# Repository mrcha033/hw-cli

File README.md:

# hw-codesign: verifiable hardware co-design release pipeline

An agent-facing CLI and MCP server for generating hardware design candidates and
proving which release checks actually ran. It is currently strongest for
**tscircuit/KiCad-backed robotics-controller flows**, not arbitrary board
topologies.

The reusable part today is the gated pipeline: typed specs, deterministic
artifacts, structured failures, provenance, and release policy. The included
component catalog, role set, and end-to-end example are centered on one STM32H7
robotics controller. Supporting a materially different board family currently
requires extending those inputs and, potentially, the generators.

> **Evidence status:** the repository includes generated Gerbers, STEP files,
> BOM, firmware, reports, and a downloadable candidate bundle. It does not yet
> claim a fabricated, electrically brought-up, thermally qualified, or EMC-tested
> board.

---

## Contents

- [Known limits](#known-limits)
- [Run it](#run-it)
- [Current scope](#current-scope)
- [First workflow](#first-workflow)
- [Generated example](#generated-example)
- [Capabilities](#capabilities)
- [Development setup](#development-setup)
- [MCP server](#mcp-server)
- [Distribution](#distribution)
- [Gate semantics](#gate-semantics)
- [Repository layout](#repository-layout)

---

## Known limits

- Three maintained board families are included: the STM32H7 robotics motor
  controller, the ESP32-S3 IoT sensor data logger, and the nRF52840 BLE sensor
  node. All component catalogs are fully reviewed; the ESP32-S3-WROOM-1 symbol
  and footprint were verified against the KiCad `RF_Module` library (2026-06-16).
- The Atopile adapter generates real `.ato` source from the electrical graph and
  runs `ato build`; the compile gate is active. When compile passes,
  `netlist_extract` and `graph_parity` are resolved via source-AST parity (signal
  declarations parsed from the `.ato` file and compared against the electrical
  graph). The three remaining post-compile gates (footprint parity, layout,
  manufacturing export) are `blocked` pending a configured KiCad plugin path.
- The `reference` and `atopile` backends are candidate-only. `tscircuit` and
  `kicad` are fabrication-release-eligible; `python_netlist` is
  netlist-release-eligible (produces `compiled_netlist.json` + firmware rather
  than Gerbers). All release paths require every configured gate to pass.
- The complete cross-domain flow depends on native KiCad, OpenCASCADE,
  Freerouting, tscircuit, and Zephyr tooling. Validated paths: Linux container
  (CI, `ubuntu-latest`), macOS (`make toolchains`), and Windows (Python test
  suite via `windows-latest` CI — native toolchains not yet installed on Windows
  runners).
- Digital gates cannot certify fabrication quality, load thermals, EMI/EMC,
  vibration, abuse safety, ingress protection, transients, or connector life.
  These physical qualification gaps are stated explicitly in every generated
  report and cannot be closed by software.
- The tracked `r1` export is historical digital evidence. The current checked-in
  `reference` configuration is candidate-only and its release gate is expected to
  remain blocked unless a compiled backend is selected and all native gates pass.

---

## Run it

**No Python required — download a standalone binary** from the
[latest release](../../releases/latest):

| Platform | File |
|---|---|
| Linux x86-64 | `hw-{version}-linux-x86_64.tar.gz` |
| macOS arm64 | `hw-{version}-macos-arm64.tar.gz` |
| Windows x86-64 | `hw-{version}-windows-x86_64.zip` |

Each archive contains `hw` (CLI) and `hw-mcp` (MCP server). macOS users must
clear Gatekeeper quarantine after download: `xattr -d com.apple.quarantine ./hw ./hw-mcp`.

These binaries are the lightweight CLI and MCP distribution. Native release gates
(KiCad fabrication, Freerouting, Zephyr) require the container or locally installed
toolchains — the same limitation as the Python package.

**Or run directly with uv** (no install):

```bash
# MCP server
HW_PLATFORM_ROOT="$PWD" uvx --from 'hw-codesign-platform[mcp]' hw-mcp

# CLI
uvx --from hw-codesign-platform hw --root . create-project quadruped_robot_controller
```

**For full toolchains** (KiCad, OpenCASCADE, Freerouting, tscircuit, Zephyr):

```bash
docker run --rm -v "$PWD:/workspace" ghcr.io/mrcha033/hw-cli:latest \
  export-review quadruped_robot_controller
```

New here? Follow [Zero to first candidate report](docs/first-run.md). Before
interpreting a green or blocked result, read the
[validation contract](docs/validation-contract.md). To change the included
design safely, read [Adapting the specification](docs/adapting-a-spec.md).

Missing `kicad-cli` returns `blocked`. Missing OpenCASCADE returns `blocked`.
A compiled error element in tscircuit returns `fail`. An unresolved critical
assumption blocks release. Decoupling proximity not yet modelled is reported as
explicitly deferred, not silently green. **Nothing is assumed to have worked.**

```json
{
  "gate": "tscircuit_compile",
  "status": "blocked",
  "failures": [{"code": "tool_unavailable", "message": "tscircuit compiler not found"}]
}
```

vs.

```json
{
  "gate": "tscircuit_compile",
  "status": "pass",
  "metrics": {"error_elements": 0, "pad_count": 183, "route_count": 217}
}
```

The difference is observable in JSON and enforced by the release gate.

---

## Current scope

A command-line and MCP-server platform that takes a structured YAML spec and
produces a release bundle — Gerbers, STEP, BOM, firmware source, Zephyr
devicetree — only after every configured gate reaches `pass`. Reference
designs produce `candidate` artifacts and are explicitly blocked from release.
Physical qualification risks (load thermals, EMI/EMC, vibration, abuse) are
stated as explicit gaps in every generated report and cannot be closed by
software.

Three reference designs are included:

- **Robotics motor controller** — 4-layer PCB, STM32H7, 12 motor channels, CAN, 24 V VBAT
- **IoT sensor data logger** — 2-layer PCB, ESP32-S3-WROOM-1, USB-C power, I2C IMU (template: `sensor_data_logger`)
- **BLE sensor node** — 2-layer PCB, nRF52840-QIAA, LiPo charging (BQ24079 + BQ27441 + AP2112K), SHT31, 50×35 mm (template: `ble_sensor_node`)

### Backend maturity

| Backend | What works | Release position |
|---|---|---|
| KiCad | Native netlist, ERC/DRC, Freerouting round trip, and manufacturing export | Fabrication-release-eligible when every native gate passes |
| tscircuit | Pinned offline compile, Circuit JSON, graph/footprint parity, placement and routing checks | Fabrication-release-eligible with the KiCad manufacturing bridge and native gates |
| python_netlist | Deterministic netlist and parity checks; produces `compiled_netlist.json` + firmware | Netlist-release-eligible; layout and manufacturing gates are N/A (not blocking) |
| reference | Generates the included design intent and candidate artifacts | Candidate-only; used for tutorials and pipeline inspection |
| Atopile | Generates real `.ato` source; compile, netlist_extract, and graph_parity gates active; source-AST parity checks declared signals vs graph | Candidate-only; footprint/layout/manufacturing blocked pending KiCad plugin path |

This is not yet universal hardware design automation. Within the included
robotics-controller family, users can change supported electrical, mechanical,
firmware, sourcing, and manufacturing parameters. A new topology requires a new
role set/component catalog and may require generator changes; see the adaptation
guide.

---

## First workflow

The shortest useful workflow intentionally ends in a `blocked` result while
still producing a reviewable candidate:

```bash
uvx --from hw-codesign-platform hw --root . create-project first_board
uvx --from hw-codesign-platform hw --root . iterate first_board --no-external
uvx --from hw-codesign-platform hw --root . export-review first_board
```

Expected result:

```json
{
  "status": "blocked",
  "iteration_id": "0001",
  "candidate": {
    "status": "candidate",
    "candidate_only": true
  }
}
```

`blocked` means the system preserved the candidate but refused to call it a
release. The command writes specs, generated intent and source, gate reports,
an iteration snapshot, and a candidate ZIP under `projects/first_board/`. The
full file map and interpretation are in the first-run guide.

---

## Generated example

The tracked robotics-controller example provides inspectable output without
requiring a local toolchain run:

- [Example and proof index](examples/robotics-motor-controller/README.md)
- [Complete generated bundle](projects/quadruped_robot_controller/exports/quadruped_robot_controller-r1.zip)
- [Gerbers](projects/quadruped_robot_controller/exports/r1/fabrication/gerbers.zip)
- [BOM](projects/quadruped_robot_controller/exports/r1/fabrication/bom.csv)
- [Assembly STEP](projects/quadruped_robot_controller/exports/r1/mechanical/assembly.step)
- [Validation report](projects/quadruped_robot_controller/exports/r1/docs/validation_report.json)
- [Known physical risks](projects/quadruped_robot_controller/exports/r1/docs/known_risks.md)

These are generated design artifacts and digital evidence, not proof of
fabrication or physical qualification. The current checked-in project spec uses
the candidate-only `reference` backend, so rerunning its current release gate is
expected to block until a compiled backend and all native gates are selected and
passed.

### Adoption milestones still open

- Publish a report screenshot or demo recording from a stable release workflow.
- Fabricate and bring up a generated board, then publish photographs, measured
  results, deviations, and the exact artifact bundle sent to manufacturing.
- Record thermal, transient, EMI/EMC, vibration, and connector qualification as
  physical evidence rather than software gate output.

---

## Capabilities

### Electronics topology authoring
- Agents author circuit blocks via `hw_add_circuit_block`: specify a ref,
  category, and connection map; the block is merged into the base topology, nets
  are re-derived, and ERC runs immediately — the gate result is returned in the
  same response
- `hw_propose_circuit_block` searches the curated component catalog by category
  and returns candidates with BOM-resolution status before any block is committed
- Agent-authored blocks stored under `agent_electronics.blocks` in
  `spec/agent_blocks.yaml`; distinct key prevents collision with `system.yaml`
  during spec merge
- ERC tolerates single-pin nets when every endpoint belongs to an agent block
  (incremental authoring support)

### Electronics backends
- Deterministic typed electrical graph with role-set resolver and curated
  component database; every resolved component has immutable provenance
- Shared source-generation step plus six-gate backend contract (compile →
  netlist → graph parity → footprint parity → layout → manufacturing export)
  enforced across all adapters
- Offline pinned **tscircuit 0.1.1491** PCB compile: Circuit JSON netlist, pad,
  placement, routing, and error-element validation
- **KiCad-native** adapter: native XML netlist extraction, ERC/DRC, Freerouting
  2.2.4 autoroute (DSN/SES round-trip), and Gerber/drill/position/BOM/STEP export
- **Python-netlist** adapter: netlist-release-eligible; produces
  `compiled_netlist.json` + firmware; layout and manufacturing gates are N/A
  rather than blocking — the release tier is explicitly `"netlist"` not fabrication
- **Atopile** adapter: emits `.ato` source and runs `ato build`; when compile
  passes, `netlist_extract` and `graph_parity` are resolved via source-AST parity;
  footprint/layout/manufacturing remain blocked pending a KiCad plugin path
- KiCad CLI and Zephyr `west` adapters with structured `tool_unavailable` reports
  when the tool is absent — they do not silently skip

### Placement
- Agent-authored placement constraints via `hw_set_placement_constraint`:
  express relationships (`adjacent_to`, `near_connector`) rather than absolute
  XY coordinates; the placer derives positions and the `placement_constraints`
  gate validates compliance immediately on write
- Constraint-driven placement proposal: structured, provenance-tagged placements
  with keepout, mounting-hole, connector-edge, decoupling-proximity, and
  thermal-spacing constraints
- Hard-blocks on off-board components, coincident centers, and connectors placed
  on the wrong board half; advisory warnings on coarse courtyard overlap and
  thermal spacing
- Decoupling proximity is represented as explicitly unenforced — cap-to-IC
  association is not in the netlist; the gate says so rather than claiming it
  checked something it did not
- Not authoritative: native ERC/DRC and the mechanical interference gate remain
  the release-blocking arbiters

### Mechanical
- Parametric 3D part design via `hw_design_part`: five part types
  (`pcb_mount_bracket`, `standoff_tower`, `cable_clip`, `din_rail_adapter`,
  `custom_enclosure_variant`), each with typed intent fields; parts are exported
  as STEP + STL with an FDM printability report (overhang, min wall, min hole)
- Spec-parameterized OpenCASCADE enclosure variants, mounting plates, frame
  brackets, connector cutouts, and board STEP assembly import/export
- Gates: valid solid, manifold STL, tolerance-aware board/component clearance,
  connector alignment, mounting-hole alignment, and measured BRep interference
  volume — nonzero interference returns `fail`
- Mechanical release requires the board STEP exported by the electronics backend;
  missing evidence returns `blocked`, not a fabricated pass

### Firmware module authoring
- Agents author firmware behavior modules via `hw_design_firmware_module`:
  four parametric behaviors (`timeout_shutdown`, `periodic_transmit`,
  `state_machine`, `sensor_poll`); each emits a `.c` file under
  `firmware/modules/` with matching Zephyr config entries
- `firmware_module_check` gate validates that every referenced signal exists in
  the pinmap; unknown signals return `fail` with specific signal names
- Signal-level cross-domain consistency checked by
  `hw_check_cross_domain_consistency`: placement constraint refs verified against
  BOM, firmware module signals verified against pinmap

### Suppliers and BOM
- Normalized curated, LCSC/JLCPCB, Digi-Key, Mouser, and Octopart-style
  supplier adapters with datasheet evidence and availability gates
- Release checks consume only in-repository snapshots under `parts/suppliers`;
  no implicit network lookup at release time
- Known out-of-stock or discontinued parts fail; missing or stale evidence blocks
- Manufacturer datasheet review evidence hashed into resolved component provenance

### Release
- Release gate requires every configured gate at `pass`, all critical assumptions
  resolved by a human, and every declared artifact present on disk with a matching
  hash
- Fabrication release: `tscircuit` and `kicad` backends (Gerber + drill + STEP);
  netlist release: `python_netlist` backend (`compiled_netlist.json` + firmware);
  `reference` and `atopile` are candidate-only

---

## Development setup

```bash
python3 -m venv .venv
.venv/bin/pip install '.[dev,mcp]'
npm ci --ignore-scripts
.venv/bin/hw --root . create-project quadruped_robot_controller
.venv/bin/hw --root . iterate quadruped_robot_controller --no-external
```

Without native toolchains all external gates return `blocked`. That is the
expected and correct output when the tools are not installed.

Install the pinned native macOS backends and run the complete flow:

```bash
make toolchains
.venv/bin/hw --root . design-until-release quadruped_robot_controller --external
```

---

## MCP server

```bash
HW_PLATFORM_ROOT="$PWD" uvx --from 'hw-codesign-platform[mcp]' hw-mcp
```

Claude Desktop configuration:

```json
{
  "mcpServers": {
    "hw-codesign": {
      "command": "uvx",
      "args": ["--from", "hw-codesign-platform[mcp]", "hw-mcp"],
      "env": {
        "HW_PLATFORM_ROOT": "/absolute/path/to/hardware-workspace"
      }
    }
  }
}
```

The configured workspace must be writable because projects, validation reports,
review bundles, and release artifacts are created beneath it.

### Canonical agent workflow

```
hw_get_capabilities          ← which backends and external tools are installed
hw_create_project / hw_open_project
hw_update_requirements       ← lowers natural-language requirements; returns release_blocking_failures

# Author topology, parts, placement, and firmware (new in Phases A–D)
hw_get_part_types            ← available parametric part types and their intent schemas
hw_design_part               ← design a 3D-printable part; returns STEP/STL + printability report
hw_propose_circuit_block     ← find catalog candidates for a given category before committing
hw_add_circuit_block         ← author a circuit block into the topology; ERC runs immediately
hw_set_placement_constraint  ← express adjacent_to / near_connector relationships; gate runs on write
hw_design_firmware_module    ← author a firmware behavior (timeout_shutdown, periodic_transmit, …)
hw_record_design_decision    ← log a decision + rationale to history/decisions.jsonl
hw_check_cross_domain_consistency ← validate placement refs against BOM, firmware signals against pinmap

hw_generate_all              ← always candidate_only=true, release_eligible=false
hw_run_all_checks            ← include_external=true for full gate matrix
hw_review_release_readiness  ← non-authoritative summary: blocking gates, requirements, assumptions
hw_generate_repair_plan / hw_apply_repair_plan / hw_resolve_assumption
hw_check_release_gate        ← release_eligible=true when status==pass
hw_export_candidate_bundle   ← archive checkpoint (candidate_only=true, release_eligible=false)
hw_export_release_bundle     ← release_eligible=true when status==released; only reachable after gate passes
```

### Response envelope

Every tool response carries a consistent envelope that enforces the core invariant:
**candidate generated ≠ release passed ≠ fabrication qualified.**

| Field | Meaning |
|---|---|
| `release_eligible` | `false` on every tool; `true` only from `hw_check_release_gate` (status `pass`) and `hw_export_release_bundle` (status `released`) |
| `candidate_only` | `true` when the backend or gate state precludes release |
| `release_blocking_failures` | always-present list of strings; empty only when no blockers are known |

`hw_review_release_readiness` additionally carries:

| Field | Meaning |
|---|---|
| `release_gate_authoritative` | always `false` — this tool reads persisted reports; only `hw_check_release_gate` is authoritative |
| `readiness_estimate` | `pass` / `fail` / `blocked` based on persisted reports; not a gate outcome |
| `data_freshness` | `current` / `possibly_stale` / `unknown` — heuristic based on spec vs report file timestamps; `possibly_stale` means the spec was modified after the last check run |

### Tools

**Platform introspection**
- `hw_get_capabilities` — available backends, external tools, and which gates each enables; call before generating
- `hw_diagnose_environment` — detailed environment probe: Python version, toolchain paths, installed packages

**Project / spec**
- `hw_create_project` — create a new project from a template
- `hw_open_project` — open an existing project and return its spec
- `hw_snapshot_project` — snapshot the current project state as a named iteration
- `hw_compare_iterations` — diff two iteration snapshots
- `hw_read_spec` — read the merged project spec
- `hw_validate_spec` — validate the spec against its JSON Schema; returns failures with field paths
- `hw_update_spec` — write a spec section; requires `user_approved=true` for safety-critical sections
- `hw_update_requirements` — lower natural-language requirements into typed spec fields; returns `release_blocking_failures` for unsupported constraints
- `hw_list_assumptions` — list all declared design assumptions and their resolution state
- `hw_resolve_assumption` — resolve a named assumption; requires `approved=true`

**Mechanical part design**
- `hw_get_part_types` — available parametric part types with their intent schemas
- `hw_design_part` — design a 3D-printable part from typed intent; returns STEP/STL + FDM printability report
- `hw_list_parts` — list all agent-designed parts for a project

**Electronics topology authoring**
- `hw_propose_circuit_block` — search component catalog by category; returns candidates before any commit
- `hw_add_circuit_block` — add or replace a circuit block in the topology; ERC gate result returned inline
- `hw_list_circuit_blocks` — list all agent-authored circuit blocks for a project

**Placement constraint authoring**
- `hw_set_placement_constraint` — author a placement relationship (`adjacent_to`, `near_connector`); placement gate runs on write
- `hw_list_placement_constraints` — list all placement constraints for a project

**Firmware module authoring**
- `hw_design_firmware_module` — author a firmware behavior module (`timeout_shutdown`, `periodic_transmit`, `state_machine`, `sensor_poll`); emits `.c` + config; signal refs checked against pinmap
- `hw_list_firmware_modules` — list all agent-designed firmware modules for a project

**Design traceability (Phase E)**
- `hw_record_design_decision` — log a decision + rationale to `history/decisions.jsonl`
- `hw_check_cross_domain_consistency` — validate placement constraint refs against BOM and firmware signal refs against pinmap; returns a GateReport

**Generation** (all emit `release_eligible: false`, `candidate_only: true`)
- `hw_generate_all` — generate electronics, mechanical, and firmware sources in one step
- `hw_generate_reference_intent` — generate reference-backend intent artifacts only
- `hw_generate_electronics_source` — generate electronics source for the configured backend
- `hw_generate_mechanical` — generate mechanical source (enclosure, mounting, fixtures)
- `hw_generate_firmware` — generate Zephyr firmware source (pinmap, devicetree, app scaffold) including any authored modules
- `hw_generate_bringup_tests` — generate bring-up test scripts from the firmware source

**Validation**
- `hw_run_all_checks` — run all configured gates; `include_external=false` skips native toolchain gates
- `hw_check_release_gate` — run the full release gate; `release_eligible=true` only when status is `pass`
- `hw_get_failure_report` — read persisted gate reports from disk; optionally filter by gate name
- `hw_run_erc` — run KiCad-native ERC; returns structured failures
- `hw_run_drc` — run KiCad-native DRC against a named fab profile
- `hw_check_electrical_semantics` — validate electrical graph semantics against spec constraints
- `hw_extract_electrical_graph` — return the resolved electrical graph JSON
- `hw_check_pinmap` — validate firmware pin assignments against the electrical graph
- `hw_check_mechanical_fit` — run mechanical clearance, interference, and alignment checks
- `hw_build_firmware` — invoke `west build` for the Zephyr target; returns structured build result

**Iteration / repair**
- `hw_run_design_iteration` — single supervised generate→check→repair cycle
- `hw_generate_repair_plan` — propose spec patches for current gate failures; includes `agent_actions` list of specific tool calls to address each failure code
- `hw_apply_repair_plan` — apply safe patches automatically; proposals requiring approval are returned, not applied
- `hw_design_until_release` — autonomous generate→check→repair loop; requires `user_approved_autonomous_iteration=true` or returns `blocked`

**Candidate management**
- `hw_export_candidate_bundle` — snapshot and ZIP the current state (`candidate_only=true`, `release_eligible=false`)
- `hw_list_candidates` — list all candidate bundles for a project
- `hw_get_candidate` — retrieve metadata for a specific candidate bundle
- `hw_review_candidate` — structured review of a candidate: gate summary, blocking failures, provenance
- `hw_compare_candidates` — diff two candidate bundles by gate status and artifact hashes

**Release readiness and export**
- `hw_review_release_readiness` — non-authoritative summary from persisted reports; check `readiness_estimate` and `data_freshness` fields
- `hw_check_release_gate` — authoritative gate; the only tool that sets `release_eligible=true`
- `hw_prepare_fabrication_review` — assemble a fabrication review package for external DFM review
- `hw_export_pcb_fabrication` — export PCB fabrication files (Gerber, drill, BOM, pick-and-place); requires KiCad native
- `hw_export_mechanical` — export STEP/STL mechanical files; requires OpenCASCADE
- `hw_import_board_step` — import an externally sourced board STEP into the mechanical assembly
- `hw_export_release_bundle` — ZIP the release directory; sets `release_eligible=true` when status is `released`
- `hw_generate_design_report` — generate a human-readable design report markdown
- `hw_verify_release` — verify artifact integrity of the release directory against its manifest

### MCP resources

URI-template resources for structured reads without tool calls:

| Resource | Contents |
|---|---|
| `hw://project/{project}/release-gate` | Non-authoritative release readiness summary (`release_gate_authoritative: false`; use `hw_check_release_gate` for the authoritative gate) |
| `hw://project/{project}/spec` | Full merged project spec |
| `hw://project/{project}/requirements` | Active requirements: lowered and unresolved constraints |

---

## Distribution

- PyPI publishes `hw-codesign-platform` from semantic-version tags using Trusted
  Publishing.
- GHCR publishes `ghcr.io/mrcha033/hw-cli` with the full native toolchain for
  `linux/amd64`.
- Each GitHub release attaches a canonical `bundle.json` and its
  `review_bundle.schema.json` contract.
- Homebrew is deferred because native system dependencies make the container a
  more reliable installation path.
- conda-forge should be reconsidered when mixed Python/system dependency support
  becomes important to broader electronics-engineering adoption.
- MCP registry publication is deferred until the public tool interface and
  versioning policy are stable.

---

## Gate semantics

| Status | Meaning |
|---|---|
| `pass` | check ran and found no blocking finding |
| `fail` | check ran and found a violation |
| `blocked` | required tooling or prior decision was absent |
| `candidate` | artifact was generated but is not release-eligible |
| `generated` | source or spec was written; does not imply gate passage or release eligibility |
| `released` | all gates passed and the release bundle was exported |

`generated` ≠ `pass` ≠ `released`. Every tool emits `release_eligible: false`
unless it is `hw_check_release_gate` (status `pass`) or `hw_export_release_bundle`
(status `released`).

The complete release, adapter, hash, and physical-evidence rules are defined in
[Validation contract](docs/validation-contract.md).

---

## Repository layout

```
src/hw_codesign/          # core platform and service layer
  backends/               # per-backend adapters (tscircuit, kicad, ...)
    firmware_modules/     # parametric firmware behavior renderers (Phase D)
    parts/                # parametric 3D part designers (Phase A)
schemas/                  # JSON Schema for spec validation
parts/                    # curated component database and supplier snapshots
projects/<name>/          # generated project workspaces
  spec/
    system.yaml           # board topology, backend, supply rails
    agent_blocks.yaml     # agent-authored circuit blocks + placement constraints
  electronics/
  mechanical/
    parts/<part_name>/    # designed 3D parts: intent.json, .step, .stl
  firmware/
    modules/              # agent-authored firmware module .c files
  history/
    decisions.jsonl       # structured design decision log (Phase E)
    iterations/
  validation/reports/
  exports/
```

Digital release evidence cannot certify load thermals, EMI/EMC, abuse safety,
vibration life, motor transients, ingress protection, or connector fatigue.
These remain explicit physical validation gaps in every generated report.

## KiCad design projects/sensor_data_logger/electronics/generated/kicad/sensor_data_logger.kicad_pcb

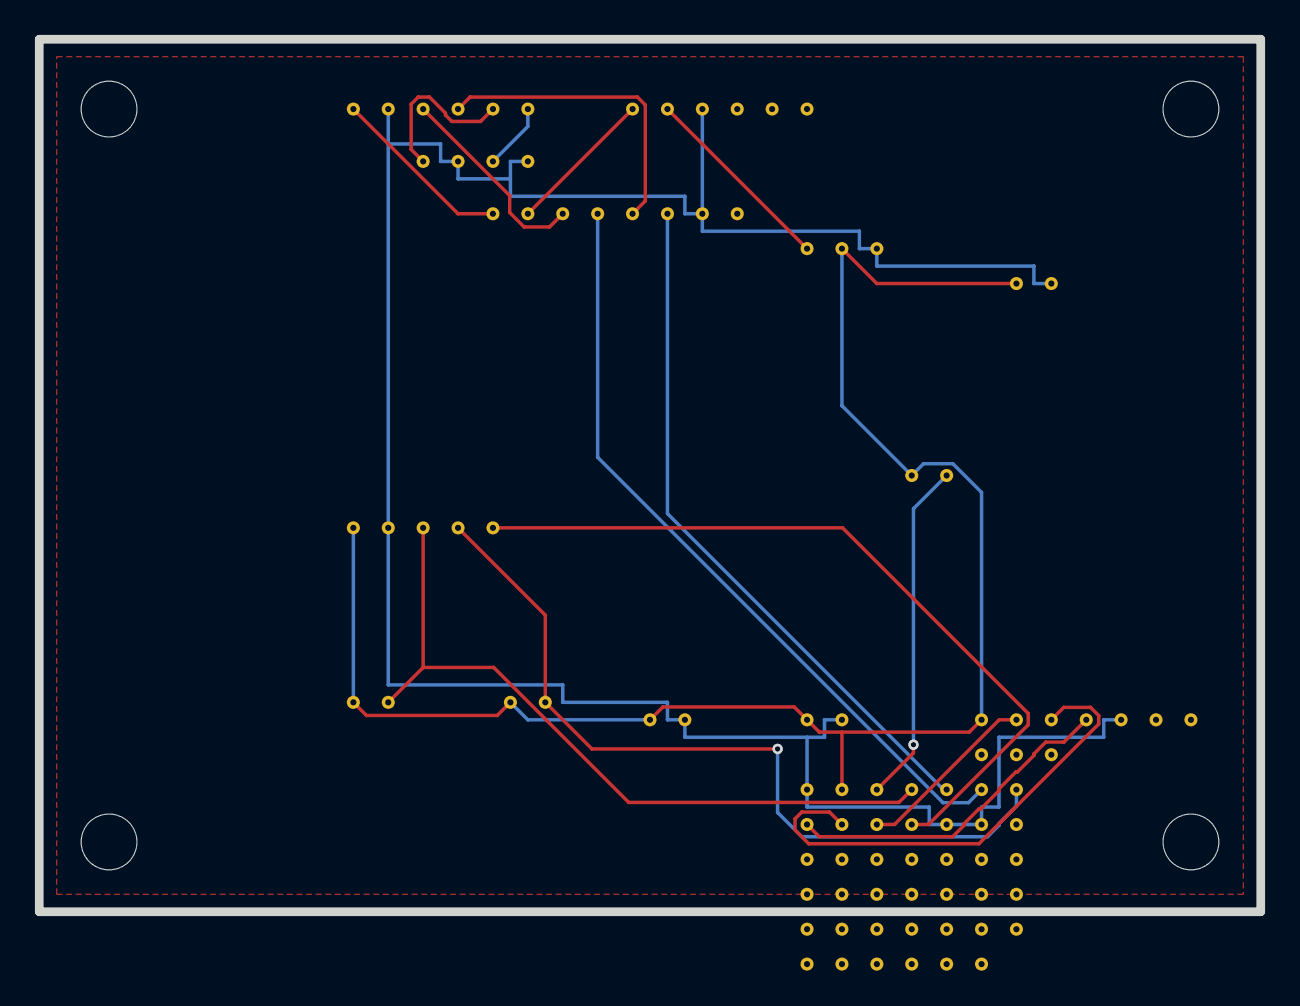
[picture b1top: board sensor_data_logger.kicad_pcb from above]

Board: 2 copper layers, 70.0 x 50.0 mm, 20 parts (0 on the bottom side), 18 nets.

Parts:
C1, C2: 100nF; C_0603_1608Metric
C9: 22uF; C_1206_3216Metric
D1: USB ESD; SOT-23-6
F1: 500mA Fuse; MIDI_Fuse
H1, H2, H3, H4: MountingHole; MountingHole_3.2mm_Pad
J1: USB-C POWER; USB_C_GCT_USB4105
J2: UART DEBUG; FTSH-105
Q1: Ideal Diode; SOT-23-6
R1, R2, R3: 4K7; R_0603_1608Metric
R5, R6: 5K1 USB-C Rd; R_0603_1608Metric
U1: ESP32-S3-WROOM-1
U2: ICM-42688-P; LGA-14
U3: 3V3 Buck; VQFN-16

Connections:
BOOT: J2.4, U1.27
ESP_EN: R3.2, U1.3
GND: C1.2, C2.2, C9.2, D1.5, J1.2, J2.5, Q1.3, R5.2, R6.2, U1.1, U1.40, U1.41, U2.2, U3.3
I2C_IMU_SCL: R1.2, U1.12, U2.3
I2C_IMU_SDA: R2.2, U1.15, U2.4
IMU_INT: U1.39, U2.5
UART_RX: J2.3, U1.36
UART_TX: J2.2, U1.37
USB_CC1: J1.5, R5.1
USB_CC2: J1.6, R6.1
USB_DM: D1.4, U1.13
USB_DM_RAW: D1.3, J1.4
USB_DP: D1.2, U1.14
USB_DP_RAW: D1.1, J1.3
USB_FUSED: F1.2, Q1.1
USB_PROT: Q1.2, U3.1
USB_VBUS: F1.1, J1.1
V3V3: C1.1, C2.1, C9.1, J2.1, R1.1, R2.1, R3.1, U1.2, U2.1, U3.2

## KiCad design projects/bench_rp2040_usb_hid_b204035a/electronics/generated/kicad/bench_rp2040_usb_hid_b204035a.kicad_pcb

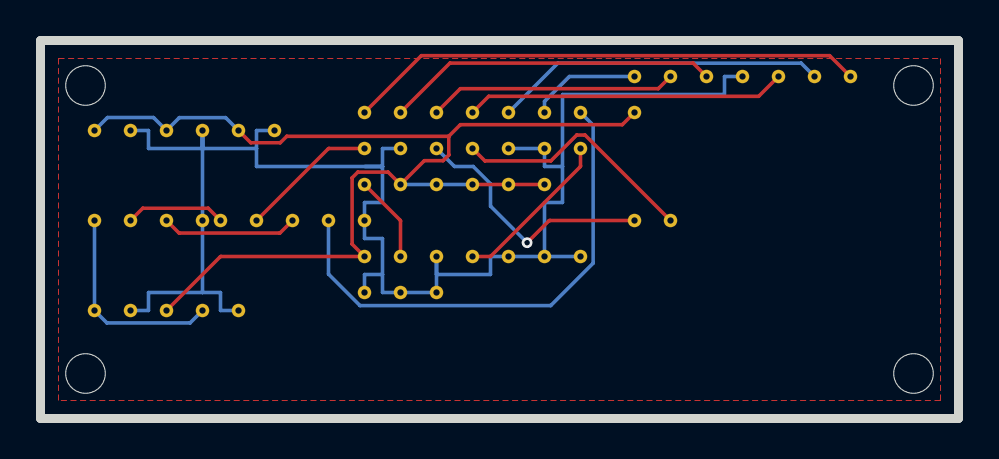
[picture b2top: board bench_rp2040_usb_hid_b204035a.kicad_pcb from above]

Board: 2 copper layers, 51.0 x 21.0 mm, 15 parts (0 on the bottom side), 17 nets.

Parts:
C1, C2: 100nF; C_0402_1005Metric
C3: 10uF; C_0603_1608Metric
C4: 10uF USB_IN; C_0603_1608Metric
D1: USB ESD; SOT-23-6
H1, H2, H3, H4: MountingHole; MountingHole_2.2mm_Pad
J1: USB-C POWER; USB_C_GCT_USB4105
J2: SWD 10-pin; PinHeader_2x05_P2.54mm_Vertical
U1: 3V3 LDO; SOT-23-5
U2: RP2040; QFN-56-1EP_7x7mm_P0.4mm_EP3.2x3.2mm
U3: 2MB QSPI; SOIC-8_3.9x4.9mm_P1.27mm
X1: 12MHz XTAL; Crystal_SMD_HC-49S

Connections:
GND: C1.2, C2.2, C3.2, C4.2, D1.5, J1.4, J2.3, J2.5, J2.6, J2.7, J2.8, J2.9, J2.10, U1.2, U2.16, U2.33, U2.34, U3.4
QSPI_CLK: U2.5, U3.6
QSPI_CS: U2.6, U3.1
QSPI_D2: U2.2, U3.3
QSPI_D3: U2.1, U3.7
QSPI_MISO: U2.3, U3.2
QSPI_MOSI: U2.4, U3.5
SWCLK: J2.4, U2.40
SWDIO: J2.2, U2.41
USB_DM: D1.4, U2.11
USB_DM_RAW: D1.3, J1.3
USB_DP: D1.2, U2.12
USB_DP_RAW: D1.1, J1.2
USB_VBUS: C4.1, J1.1, U1.1
V3V3: C1.1, C2.1, C3.1, J2.1, U1.3, U2.44, U2.45, U2.46, U2.47, U2.48, U3.8
XIN: U2.17, X1.1
XOUT: U2.18, X1.2

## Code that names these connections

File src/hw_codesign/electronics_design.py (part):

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    dp_net = "USB_DP_RAW" if raw_data else "USB_DP"
    dm_net = "USB_DM_RAW" if raw_data else "USB_DM"
    return [
        pin(1, "VBUS", "USB_VBUS", "power_in"),
        pin(2, "GND", "GND", "ground"),
        pin(3, "D+", dp_net, "bidirectional"),
        pin(4, "D-", dm_net, "bidirectional"),
        pin(5, "CC1", "USB_CC1", "passive"),
        pin(6, "CC2", "USB_CC2", "passive"),
    ]


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            "5K1 USB-C Rd",
            "RC0603FR-075K1L",
            "R0603",
            [pin(1, "A", "USB_CC1", "passive"), pin(2, "B", "GND", "ground")],
            manufacturer="Yageo",
            substitute_mpn="CRCW06035K10FKEA",
        ),
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            "5K1 USB-C Rd",
            "RC0603FR-075K1L",
            "R0603",
            [pin(1, "A", "USB_CC2", "passive"), pin(2, "B", "GND", "ground")],
            manufacturer="Yageo",
            substitute_mpn="CRCW06035K10FKEA",
        ),
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    signal_nets = ["ESTOP_IN", "CAN_RX", "CAN_TX", "I2C_IMU_SCL", "I2C_IMU_SDA", "IMU_INT", "SWDIO", "SWCLK", "NRST", "USB_DP", "USB_DM"]
    for index in range(1, channels + 1):
        signal_nets.extend((f"MOTOR{index}_PWM", f"MOTOR{index}_CURRENT", f"MOTOR{index}_ENC"))
    mcu_pins = [pin(1, "VDD", "V3V3", "power_in"), pin(2, "VSS", "GND", "ground")]
    for number, net in enumerate(signal_nets, 3):
        role = "analog" if net.endswith("CURRENT") else "bidirectional"
        mcu_pins.append(pin(number, net, net, role))
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        component("D1", "tvs", "33V TVS", "SMCJ33A", "SMCJ", [pin(1, "K", "VBAT", "passive"), pin(2, "A", "GND", "ground")], manufacturer="Littelfuse", substitute_mpn="SMCJ33A-E3/57T"),
        component("U3", "efuse", "eFuse", "TPS26630RGET", "VQFN24", [pin(1, "IN", "VBAT", "power_in"), pin(2, "OUT", "VSYS", "power_out"), pin(3, "GND", "GND", "ground"), pin(4, "SHDN", "ESTOP_GATE", "input")], manufacturer="Texas Instruments", substitute_mpn="LTC4368IDD-2"),
        component("U4", "regulator", "5V Buck", "LM76005RNPR", "WQFN30", [pin(1, "VIN", "VSYS", "power_in"), pin(2, "VOUT", "V5", "power_out"), pin(3, "GND", "GND", "ground")], manufacturer="Texas Instruments", substitute_mpn="LT8645SIV"),
        component("U5", "regulator", "3V3 Buck", "TPS62133RGTR", "VQFN16", [pin(1, "VIN", "V5", "power_in"), pin(2, "VOUT", "V3V3", "power_out"), pin(3, "GND", "GND", "ground")], manufacturer="Texas Instruments", substitute_mpn="AP63203WU-7"),
        component("U1", "mcu", "STM32H743", "STM32H743VIT6", "LQFP100", mcu_pins, manufacturer="STMicroelectronics", substitute_mpn="STM32H753VIT6"),
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        component("J2", "estop", "E-STOP", "Phoenix-1935161", "Terminal_3Pin", [pin(1, "V3V3", "V3V3", "power_out"), pin(2, "ESTOP", "ESTOP_IN", "input"), pin(3, "GND", "GND", "ground")], manufacturer="Phoenix Contact", substitute_mpn="WAGO-250-203"),
        component("Q2", "safety_gate", "E-STOP GATE", "SN74LVC1G97DBVR", "SOT23-6", [pin(1, "VCC", "V3V3", "power_in"), pin(2, "IN", "ESTOP_IN", "input"), pin(3, "OUT", "ESTOP_GATE", "output"), pin(4, "GND", "GND", "ground")], manufacturer="Texas Instruments", substitute_mpn="74LVC1G97GV"),
        component("J3", "can_connector", "CAN", "Molex-43650-0300", "MicroFit_3Pin", [pin(1, "CANH", "CANH", "bidirectional"), pin(2, "CANL", "CANL", "bidirectional"), pin(3, "GND", "GND", "ground")], manufacturer="Molex", substitute_mpn="Phoenix-1935174"),
        component("R1", "termination", "120R", "RC0603FR-07120RL", "R0603", [pin(1, "A", "CANH", "passive"), pin(2, "B", "CANL", "passive")], manufacturer="Yageo", substitute_mpn="CRCW0603120RFKEA"),
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        component("J5", "usb", "USB-C", "USB4105-GF-A", "USB_C_16Pin", usb_c_connector_pins(raw_data=True), manufacturer="GCT", substitute_mpn="USB4085-GF-A"),
        *usb_c_rd_components(5),
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        component("R4", "discharge", "100K", "RC0603FR-07100KL", "R0603", [pin(1, "VBUS", "USB_VBUS", "passive"), pin(2, "GND", "GND", "ground")], manufacturer="Yageo", substitute_mpn="CRCW0603100KFKEA"),
        component("R2", "pullup", "4K7", "RC0603FR-074K7L", "R0603", [pin(1, "VCC", "V3V3", "passive"), pin(2, "SCL", "I2C_IMU_SCL", "passive")], manufacturer="Yageo", substitute_mpn="CRCW06034K70FKEA"),
        component("R3", "pullup", "4K7", "RC0603FR-074K7L", "R0603", [pin(1, "VCC", "V3V3", "passive"), pin(2, "SDA", "I2C_IMU_SDA", "passive")], manufacturer="Yageo", substitute_mpn="CRCW06034K70FKEA"),
    ]
    for index in range(1, channels + 1):
        components.append(component(f"J{index + 10}", "motor_io", f"MOTOR_IO_{index}", "Molex-43045-0800", "MicroFit_8Pin", [
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            pin(4, "CURRENT", f"MOTOR{index}_CURRENT", "analog"), pin(5, "ENC", f"MOTOR{index}_ENC", "input"), pin(6, "ESTOP", "ESTOP_GATE", "output"),
        ], manufacturer="Molex", substitute_mpn="Molex-43025-0800"))
    for index in range(1, 9):
        components.append(component(f"C{index}", "decoupling", "100nF", "GRM188R71C104KA01D", "C0603", [pin(1, "VCC", "V3V3", "passive"), pin(2, "GND", "GND", "ground")], manufacturer="Murata", substitute_mpn="CC0603KRX7R9BB104"))
    components.extend((
        component("C9", "bulk_cap", "22uF", "GRM31CR61E226ME15L", "C1206", [pin(1, "VCC", "V5", "passive"), pin(2, "GND", "GND", "ground")], manufacturer="Murata", substitute_mpn="CL31A226KAHNNNE"),
        component("C10", "bulk_cap", "10uF 50V", "GRM32ER71H106KA12L", "C1210", [pin(1, "VCC", "VSYS", "passive"), pin(2, "GND", "GND", "ground")], manufacturer="Murata", substitute_mpn="C3225X7R1H106K250AB"),
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        component("J1", "power_input", "USB-C POWER", "USB4105-GF-A", "USB_C_16Pin", usb_c_connector_pins(raw_data=True), manufacturer="GCT"),
        *usb_c_rd_components(5),
        component("F1", "fuse", "500mA Fuse", "Littelfuse-0498080.M", "MIDI", [
            pin(1, "IN", "USB_VBUS", "passive"),
            pin(2, "OUT", "USB_FUSED", "passive"),
        ], manufacturer="Littelfuse"),
        component("Q1", "reverse_polarity", "Ideal Diode", "LM74700QDBVRQ1", "SOT23-6", [
            pin(1, "ANODE", "USB_FUSED", "power_in"),
            pin(2, "CATHODE", "USB_PROT", "power_out"),
            pin(3, "GND", "GND", "ground"),
        ], manufacturer="Texas Instruments"),
        component("D1", "tvs", "USB ESD", "USBLC6-2SC6", "SOT23-6", [
            pin(1, "DP_IN", "USB_DP_RAW", "bidirectional"),
            pin(2, "DP_OUT", "USB_DP", "bidirectional"),
            pin(3, "DM_IN", "USB_DM_RAW", "bidirectional"),
            pin(4, "DM_OUT", "USB_DM", "bidirectional"),
            pin(5, "GND", "GND", "ground"),
        ], manufacturer="STMicroelectronics"),
        component("U3", "regulator", "3V3 Buck", "TPS62133RGTR", "VQFN16", [
            pin(1, "VIN", "USB_PROT", "power_in"),
            pin(2, "VOUT", "V3V3", "power_out"),
            pin(3, "GND", "GND", "ground"),
        ], manufacturer="Texas Instruments"),
        component("U1", "mcu", "ESP32-S3-WROOM-1", "ESP32-S3-WROOM-1-N8", "RF_Module:ESP32-S3-WROOM-1", [
            pin(1, "GND", "GND", "ground"),
            pin(2, "3V3", "V3V3", "power_in"),
            {**pin(3, "EN", "ESP_EN", "input"), "mcu_pin": "EN"},
            {**pin(12, "IO8", "I2C_IMU_SCL", "open_drain"), "mcu_pin": "GPIO8"},
            {**pin(13, "USB_D-", "USB_DM", "bidirectional"), "mcu_pin": "USB_D-"},
            {**pin(14, "USB_D+", "USB_DP", "bidirectional"), "mcu_pin": "USB_D+"},
            {**pin(15, "IO3", "I2C_IMU_SDA", "open_drain"), "mcu_pin": "GPIO3"},
            {**pin(27, "IO0", "BOOT", "input"), "mcu_pin": "GPIO0"},
            {**pin(36, "RXD0", "UART_RX", "input"), "mcu_pin": "RXD0"},
            {**pin(37, "TXD0", "UART_TX", "output"), "mcu_pin": "TXD0"},
            {**pin(39, "IO1", "IMU_INT", "input"), "mcu_pin": "GPIO1"},
            pin(40, "GND", "GND", "ground"),
            pin(41, "GND", "GND", "ground"),
        ], manufacturer="Espressif Systems"),
        component("U2", "imu", "ICM-42688-P", "ICM-42688-P", "LGA14", [
            pin(1, "VDD", "V3V3", "power_in"),
            pin(2, "GND", "GND", "ground"),
            pin(3, "SCL", "I2C_IMU_SCL", "open_drain"),
            pin(4, "SDA", "I2C_IMU_SDA", "open_drain"),
            pin(5, "INT1", "IMU_INT", "output"),
        ], manufacturer="TDK InvenSense"),
        component("J2", "debug", "UART DEBUG", "Samtec-FTSH-105-01-L-DV-K", "Cortex_Debug_10Pin", [
            pin(1, "VREF", "V3V3", "power_out"),
            pin(2, "TXD", "UART_TX", "output"),
            pin(3, "RXD", "UART_RX", "input"),
            pin(4, "BOOT", "BOOT", "input"),
            pin(5, "GND", "GND", "ground"),
        ], manufacturer="Samtec"),
        component("R1", "pullup", "4K7", "RC0603FR-074K7L", "R0603", [pin(1, "VCC", "V3V3", "passive"), pin(2, "SCL", "I2C_IMU_SCL", "passive")], manufacturer="Yageo"),
        component("R2", "pullup", "4K7", "RC0603FR-074K7L", "R0603", [pin(1, "VCC", "V3V3", "passive"), pin(2, "SDA", "I2C_IMU_SDA", "passive")], manufacturer="Yageo"),
        component("R3", "pullup", "4K7", "RC0603FR-074K7L", "R0603", [pin(1, "VCC", "V3V3", "passive"), pin(2, "EN", "ESP_EN", "passive")], manufacturer="Yageo"),
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
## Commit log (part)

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2026-06-14 fix: six correctness issues — gate names, sourcing schema, Zephyr board, frozen release reports, tscircuit PCB gates
    - Rename internal IR gates: "erc"→"ir_erc" and "drc"→"ir_pcb_sanity" so
    they cannot be confused with native_erc/native_drc from KiCad CLI
    - Fix Zephyr backend: replace hardcoded -DBOARD=nucleo_h743zi with the
    board parameter passed at call time
    - Fix check_sourcing(): access sourcing.supplier_skus (nested dict from
    resolver) instead of the nonexistent top-level supplier_sku; replace
2026-06-14 Refactor code structure for improved readability and maintainability
2026-06-15 fix: enforce 90-day staleness threshold on supplier availability evidence
    The README claimed "stale evidence blocks" but the resolver only checked
    whether observed_at was present, not whether it was recent. A 2019 snapshot
    with availability: available would pass the gate.
    Add SUPPLIER_EVIDENCE_MAX_AGE_DAYS = 90 and _evidence_is_stale() which
    parses the ISO-8601 timestamp and returns blocked + supplier_evidence_stale
    when the snapshot is older than the threshold or unparseable. Two new tests:
2026-06-15 feat: add hw serve-review local web viewer with comments JSONL sidecar (steps 5-6)
    review_viewer.py serves the review bundle over stdlib http.server on
    localhost:7474. The viewer fetches /api/bundle dynamically and auto-
    refreshes every 30 s. POST /api/comment appends to a comments.jsonl
    sidecar keyed by the bundle path, then re-injects the accumulated comments
    into the live bundle so the viewer shows them on next refresh.
    The sidecar is mutable and intentionally kept separate from the immutable
2026-06-15 feat: topology-aware validation, real atopile adapter, schema generalization
    Continuation of the second board family and atopile upgrade commit.
2026-06-16 feat: nRF52840 BLE sensor topology, fabrication improvements, mechanical depth
    Third board family:
    - nRF52840-QIAA (Cortex-M4F + BLE 5.0) on 50x35mm 2-layer PCB
    - BQ24079 LiPo charger, BQ27441 fuel gauge, AP2112K LDO, SHT31 env sensor
    - Curated component library (ble_sensor_node.yaml) + role set + datasheets
    - Zephyr BLE firmware profile: CONFIG_BT, test_ble_adv.c, test_i2c_sensors.c
    - 9 new tests covering graph, ERC, placement, pinmap parity, firmware, release
2026-06-17 docs: update README and adapting-a-spec for Phases A–E authoring tools
2026-06-21 feat: validation — power-tree integrity, interface integrity, and pin-net mismatch detection
    check_graph_pin_resolution gains a pin-net consistency cross-check: it now detects when a net
    claims a pin that the component itself assigns to a different net (graph_pin_net_mismatch), not
    just when a pin reference is absent. check_power_tree traces reachability from power-source
    components through fuse/regulator/eFuse transfer paths and flags disconnected rails, missing
    transfer pins, and voltage-domain mismatches on power and ground pins. check_interface_integrity
    verifies SPI/I2C/UART/CAN net groupings and detects incomplete bus wiring. Helper functions for
2026-06-21 feat: placement — layout thermal integrity and signal-integrity checks
    check_layout_thermal_integrity catches high-level contradictions before physical qualification:
    high-current designs on under-layered stackups, thermal-risk components placed too close to
    sensitive devices (MCU, IMU, fuel gauge), under-rated motor connectors, and spread-out ingress
    chains. check_layout_signal_integrity validates RF antenna edge proximity, RF keepout violations
    near noisy power components, and USB ESD placement distance. Both gates are wired into
    run_all_checks and emitted to the release bundle. Constants for risk categories, thresholds, and
2026-06-21 feat: generators — semantic schematic output (JSON + executable Python)
    generate_all now writes a semantic schematic alongside the electrical graph. The JSON layer
    (_write_semantic_schematic) captures components, nets, and pin-name connections in a
    design-intent representation independent of footprint coordinates. A companion Python module
    (_semantic_schematic_code) emits an executable semantic_schematic.py whose eval must reproduce
    the JSON exactly; the roundtrip is verified by the semantic_schematic_roundtrip gate in service.
2026-06-21 feat: service — design_candidate, design-space exploration, physical qualification, and new release gates
    design_candidate generates a cross-domain hardware candidate, packages reviewable artifacts, and
    returns a grounding summary without attempting release promotion. explore_design_space enumerates
    backend, component, mechanical, and supplier axes and scores each against the current gates.
    generate_physical_qualification_plan emits a structured test plan (JSON + Markdown) from the spec
    and graph; record_physical_evidence ingests approved bench measurements against it. run_grounding_benchmark
    mutates the live graph in targeted ways and checks that the expected gate codes fire.
2026-06-28 fix: schematic_generator row spacing 18mm→30.48mm prevents ERC pin-collision
    With 18mm row pitch, a Conn_01x08 (8-pin symbol) extends 10.16mm below its
    center while the next 9-pin symbol extends 10.16mm above its center — they
    overlap by 2.54mm when only 18mm apart. The collision creates two labels on
    the same wire endpoint, triggering KiCad ERC multiple_net_names violations.
    30.48mm (12×2.54mm) gives 10.16mm clearance for adjacent ≤12-pin components.
2026-06-29 fix: prevent placement solver from violating mounting-hole keepouts
    Four benchmark regressions addressed:
    - placement.py: add mounting_hole_keepout term (500×/mm) to _placement_cost
    so the solver never moves components inside hole clearance zones
    - validation.py: guard assumptions iteration with isinstance(dict) to handle
    rp2040 templates that store assumptions as a list instead of a dict
    - zephyr.py: add nrf52840dk entry to _BOARD_EXTRA_MODULES and fix
2026-06-30 feat: validate category pin role contracts
2026-06-30 feat: ground rp2040 qspi schematic generation
2026-06-30 fix: model rp2040 usb esd boundary
2026-06-30 fix: ground rp2040 power path evidence
2026-06-30 feat: add traceable requirements compiler tokens
